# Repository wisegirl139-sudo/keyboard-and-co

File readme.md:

<h2 align="centre">Keyboard & co</h2>
hi,welcome to my little disaterously organised project, now keyboard&co is a modular keyboard made by Oliver and me , now im good at websites and schmatics apparently but pcbs are not my thinggg. 
the modular keyboard uses a esp32 s3 vroom , and pogo pins i think theyre called to connect each part of the keyboard. then it uses the same switches as a hack pad. bom etc is to come soon , journal rn is time lapses but will be fully updated by next ship
<h4>SCH</h4>

okay well that was that , now for my expertise which is web dev , i present to u the most me website i have ever made. it has media pipe for gesture control , yes its gesture controlled yeas u can flip off the laptop , it scrolls the page, maybe give it a thumbs up to select or pinc to zoomin
also featuring my veryyy creapy art lowk
its meant to be a keycap with hena bc happy diwali everyone!!
im not the best artist but atleast i have hope ig
anyways libraries used were ediapipe and three.js for the 3d models made by oliver , u can add and interact with them using ur cursor too!! and download files does spam you but its cool
anyways that all for now, gonna finish journal then yes adios

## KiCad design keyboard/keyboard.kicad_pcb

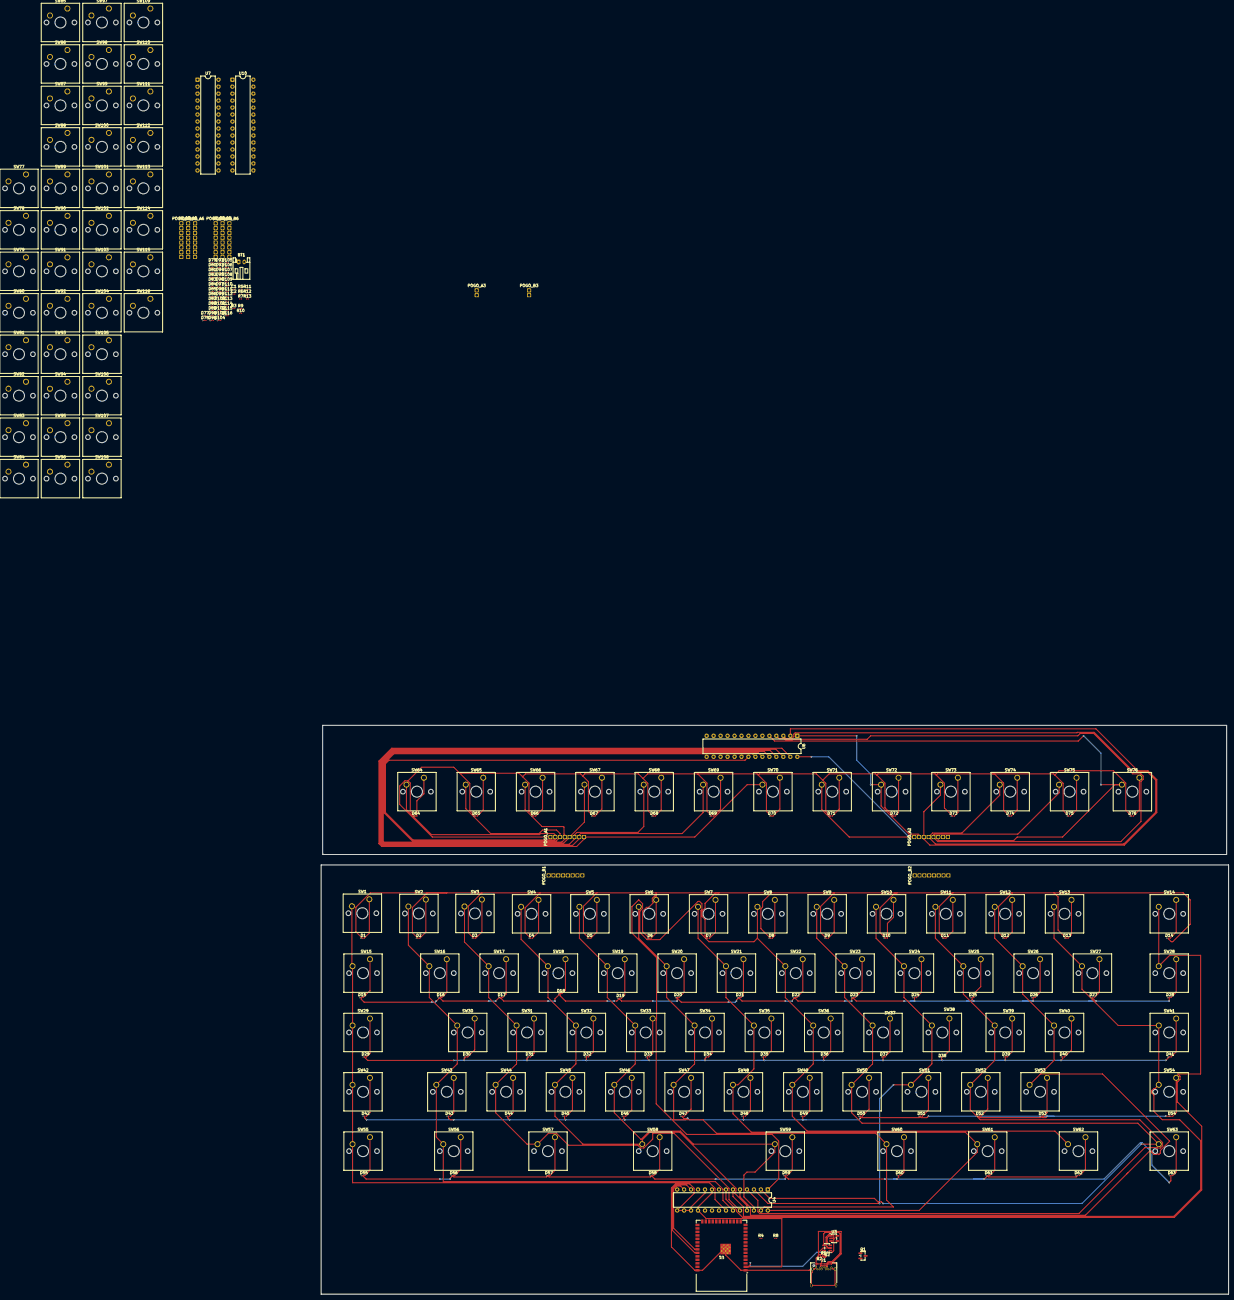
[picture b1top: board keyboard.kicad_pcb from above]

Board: 2 copper layers, 330.2 x 207.0 mm, 269 parts (0 on the bottom side), 189 nets.

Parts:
BT1: Battery_Cell; JST_PH_S2B-PH-K_1x02_P2.00mm_Horizontal
C1: 10uf; C_0201_0603Metric
C2: 100n; C_0201_0603Metric
D1, D2, D3, D4, D5, D6, D7, D8, D9, D10, D11, D12, D13, D14, D15, D16, D17, D18, D19, D20, D21, D22, D23, D24, D25, D26, D27, D28, D29, D30, D31, D32, D33, D34, D35, D36, D37, D38, D39, D40, D41, D42, D43, D44, D45, D46, D47, D48, D49, D50, D51, D52, D53, D54, D55, D56, D57, D58, D59, D60, D61, D62, D63, D64, D65, D66, D67, D68, D69, D70, D71, D72, D73, D74, D75, D76, D77, D78, D79, D80, D81, D82, D83, D84, D85, D86, D87, D88, D89, D90, D91, D92, D93, D94, D95, D96, D97, D98, D99, D100, D101, D102, D103, D104, D105, D106, D107, D108, D109, D110, D111, D112, D113, D114, D115, D116: LED; LED_0201_0603Metric
J1: USB_C_Receptacle; USB_C_Receptacle_Amphenol_12401548E4-2A
POGO_A1, POGO_A2, POGO_A4, POGO_A5, POGO_A6: 8_Pin
POGO_A3: 2_Pin
POGO_B1, POGO_B2, POGO_B4, POGO_B5, POGO_B6: 8_Pin
POGO_B3: 2_Pin
Q1: AO3401A; SOT-23
R1: R; R_0201_0603Metric
R2, R3: 5.1k; R_0201_0603Metric
R4, R5, R8: 100k; R_0201_0603Metric
R6, R7, R10, R11, R12, R13: 4.7k; R_0201_0603Metric
R9: 330; R_0201_0603Metric
SW1, SW2, SW3, SW4, SW5, SW6, SW7, SW8, SW9, SW10, SW11, SW12, SW13, SW14, SW15, SW16, SW17, SW18, SW19, SW20, SW21, SW22, SW23, SW24, SW25, SW26, SW27, SW28, SW29, SW30, SW31, SW32, SW33, SW34, SW35, SW36, SW37, SW38, SW39, SW40, SW41, SW42, SW43, SW44, SW45, SW46, SW47, SW48, SW49, SW50, SW51, SW52, SW53, SW54, SW55, SW56, SW57, SW58, SW59, SW60, SW61, SW62, SW63, SW64, SW65, SW66, SW67, SW68, SW69, SW70, SW71, SW72, SW73, SW74, SW75, SW76, SW77, SW78, SW79, SW80, SW81, SW82, SW83, SW84, SW85, SW86, SW87, SW88, SW89, SW90, SW91, SW92, SW93, SW94, SW95, SW96, SW97, SW98, SW99, SW100, SW101, SW102, SW103, SW104, SW105, SW106, SW107, SW108, SW109, SW110, SW111, SW112, SW113, SW114, SW115, SW116: SW_Push; SW_Cherry_MX_1.00u_PCB
U1: ESP32-S3-WROOM-1
U2: MCP73831-2-OT; SOT-23-5
U3: AP2112K-3.3; SOT-23-5
U4, U6, U7, U10: MCP23017x-x-SP; DIP-28_W7.62mm

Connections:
+3V3: C1.2, C2.1, POGO_A6.1, POGO_B6.1, R6.2, R7.2, R10.2, R11.2, R12.2, R13.2, U1.2 (3V3), U3.5 (VOUT), U4.9 (V_{DD}), U4.18 (~RESET), U6.9 (V_{DD}), U6.18 (~RESET), U7.9 (V_{DD}), U7.18 (~RESET), U10.9 (V_{DD}), U10.15 (A0), U10.18 (~RESET)
+5V: J1.A4 (VBUS), J1.A9 (VBUS), J1.B4 (VBUS), J1.B9 (VBUS), U2.4 (V_{DD})
C0: POGO_A1.2, POGO_B1.2, SW64.2, U6.21 (GPA0)
C1: POGO_A1.3, POGO_B1.3, SW65.2, U6.22 (GPA1)
C2: POGO_A1.4, POGO_B1.4, SW66.2, U6.23 (GPA2)
C3: POGO_A1.5, POGO_B1.5, SW67.2, U6.24 (GPA3)
C4: POGO_A1.6, POGO_B1.6, SW68.2, U6.25 (GPA4)
C5: POGO_A1.7, POGO_B1.7, SW69.2, U6.26 (GPA5)
C6: POGO_A1.8, POGO_B1.8, SW70.2, U6.27 (GPA6)
C7: POGO_A2.1, POGO_B2.1, SW71.2, U6.28 (GPA7)
C8: POGO_A2.2, POGO_B2.2, SW72.2, U6.1 (GPB0)
C9: POGO_A2.3, POGO_B2.3, SW73.2, U6.2 (GPB1)
C10: POGO_A2.4, POGO_B2.4, SW74.2, U6.3 (GPB2)
C11: POGO_A2.5, POGO_B2.5, SW75.2, U6.4 (GPB3)
C12: POGO_A2.6, POGO_B2.6, SW76.2, U6.5 (GPB4)
GND: BT1.1 (+), C1.1, C2.2, J1.A1 (GND), J1.A12 (GND), J1.B1 (GND), J1.B12 (GND), J1.SH (SHIELD), POGO_A2.8, POGO_A3.2, POGO_A4.8, POGO_A6.2, POGO_A6.8, POGO_B2.8, POGO_B3.2, POGO_B4.8, POGO_B6.2, POGO_B6.8, R1.2, R2.2, R3.2, R5.1, U1.1 (GND), U1.40 (GND), U1.41 (GND), U2.2 (V_{SS}), U3.2 (GND), U4.10 (V_{SS}), U4.15 (A0), U4.16 (A1), U4.17 (A2), U6.10 (V_{SS}), U6.15 (A0), U6.16 (A1), U6.17 (A2), U7.10 (V_{SS}), U7.15 (A0), U7.16 (A1), U7.17 (A2), U10.10 (V_{SS}), U10.16 (A1), U10.17 (A2)
unnamed: D1.2 (A), SW1.1
unnamed: D2.2 (A), SW2.1
unnamed: D3.2 (A), SW3.1
unnamed: D4.2 (A), SW4.1
unnamed: D5.2 (A), SW5.1
unnamed: D6.2 (A), SW6.1
unnamed: D7.2 (A), SW7.1
unnamed: D8.2 (A), SW8.1
unnamed: D9.2 (A), SW9.1
unnamed: D10.2 (A), SW10.1
unnamed: D11.2 (A), SW11.1
unnamed: D12.2 (A), SW12.1
unnamed: D13.2 (A), SW13.1
unnamed: D14.2 (A), SW14.1
unnamed: D15.2 (A), SW15.1
unnamed: D16.2 (A), SW16.1
unnamed: D17.2 (A), SW17.1
unnamed: D18.2 (A), SW18.1
unnamed: D19.2 (A), SW19.1
unnamed: D20.2 (A), SW20.1
unnamed: D21.2 (A), SW21.1
unnamed: D22.2 (A), SW22.1
unnamed: D23.2 (A), SW23.1
unnamed: D24.2 (A), SW24.1
unnamed: D25.2 (A), SW25.1
unnamed: D26.2 (A), SW26.1
unnamed: D27.2 (A), SW27.1
unnamed: D28.2 (A), SW28.1
unnamed: D29.2 (A), SW29.1
unnamed: D30.2 (A), SW30.1
unnamed: D31.2 (A), SW31.1
unnamed: D32.2 (A), SW32.1
unnamed: D33.2 (A), SW33.1
unnamed: D34.2 (A), SW34.1
unnamed: D35.2 (A), SW35.1
unnamed: D36.2 (A), SW36.1
unnamed: D37.2 (A), SW37.1
unnamed: D38.2 (A), SW38.1
unnamed: D39.2 (A), SW39.1
unnamed: D40.2 (A), SW40.1
unnamed: D41.2 (A), SW41.1
unnamed: D42.2 (A), SW42.1
unnamed: D43.2 (A), SW43.1
unnamed: D44.2 (A), SW44.1
unnamed: D45.2 (A), SW45.1
unnamed: D46.2 (A), SW46.1
unnamed: D47.2 (A), SW47.1
unnamed: D48.2 (A), SW48.1
unnamed: D49.2 (A), SW49.1
unnamed: D50.2 (A), SW50.1
unnamed: D51.2 (A), SW51.1
unnamed: D52.2 (A), SW52.1
unnamed: D53.2 (A), SW53.1
unnamed: D54.2 (A), SW54.1
unnamed: D55.2 (A), SW55.1
unnamed: D56.2 (A), SW56.1
unnamed: D57.2 (A), SW57.1
unnamed: D58.2 (A), SW58.1
unnamed: D59.2 (A), SW59.1
unnamed: D60.2 (A), SW60.1
unnamed: D61.2 (A), SW61.1
unnamed: D62.2 (A), SW62.1
unnamed: D63.2 (A), SW63.1
unnamed: D64.2 (A), SW64.1
unnamed: D65.2 (A), SW65.1
unnamed: D66.2 (A), SW66.1
unnamed: D67.2 (A), SW67.1
unnamed: D68.2 (A), SW68.1
unnamed: D69.2 (A), SW69.1
unnamed: D70.2 (A), SW70.1
unnamed: D71.2 (A), SW71.1
unnamed: D72.2 (A), SW72.1
unnamed: D73.2 (A), SW73.1
unnamed: D74.2 (A), SW74.1
unnamed: D75.2 (A), SW75.1
unnamed: D76.2 (A), SW76.1
unnamed: D77.2 (A), SW77.1
unnamed: D78.2 (A), SW78.1
unnamed: D79.2 (A), SW79.1
unnamed: D80.2 (A), SW80.1
unnamed: D81.2 (A), SW81.1
unnamed: D82.2 (A), SW82.1
unnamed: D83.2 (A), SW83.1
unnamed: D84.2 (A), SW86.1
unnamed: D85.2 (A), SW89.1
unnamed: D86.2 (A), SW93.1
unnamed: D87.2 (A), SW94.1
unnamed: D88.2 (A), SW95.1
unnamed: D89.2 (A), SW92.1
unnamed: D90.2 (A), SW90.1
unnamed: D91.2 (A), SW87.1
unnamed: D92.2 (A), SW84.1
unnamed: D93.2 (A), SW85.1
unnamed: D94.2 (A), SW88.1
unnamed: D95.2 (A), SW91.1
unnamed: D96.2 (A), SW96.1
unnamed: D97.2 (A), SW97.1
unnamed: D98.2 (A), SW98.1
unnamed: D99.2 (A), SW99.1
unnamed: D100.2 (A), SW100.1
unnamed: D101.2 (A), SW101.1
unnamed: D102.2 (A), SW102.1
unnamed: D103.2 (A), SW103.1
unnamed: D104.2 (A), SW104.1
unnamed: D105.2 (A), SW105.1
unnamed: D106.2 (A), SW106.1
unnamed: D107.2 (A), SW107.1
unnamed: D108.2 (A), SW108.1
unnamed: D109.2 (A), SW109.1
unnamed: D110.2 (A), SW110.1
unnamed: D111.2 (A), SW111.1
unnamed: D112.2 (A), SW112.1
unnamed: D113.2 (A), SW113.1
unnamed: D114.2 (A), SW114.1
unnamed: D115.2 (A), SW115.1
unnamed: D116.2 (A), SW116.1
unnamed: J1.A5 (CC1), R2.1
unnamed: J1.B5 (CC2), R3.1
unnamed: R9.2, U1.38 (IO2)
unnamed: R1.1, U2.5 (PROG)
R0: D64.1 (K), D65.1 (K), D66.1 (K), D67.1 (K), D68.1 (K), D69.1 (K), D70.1 (K), D71.1 (K), D72.1 (K), D73.1 (K), D74.1 (K), D75.1 (K), D76.1 (K), POGO_A1.1, POGO_B1.1
adc: R4.1, R5.2, U1.39 (IO1)
bat: BT1.2 (-), Q1.2 (S), R4.2, R8.1, U2.3 (V_{BAT}), U3.1 (VIN)
c0: SW1.2, SW15.2, SW29.2, SW42.2, SW55.2, U4.22 (GPA1)
c1: SW2.2, SW16.2, SW30.2, SW43.2, SW56.2, U4.23 (GPA2)
c2: SW3.2, SW17.2, SW31.2, SW44.2, SW57.2, U4.24 (GPA3)
c3: SW4.2, SW18.2, SW32.2, SW45.2, SW58.2, U4.25 (GPA4)
c4: SW5.2, SW19.2, SW33.2, SW46.2, SW59.2, U4.26 (GPA5)
c5: SW6.2, SW20.2, SW34.2, SW47.2, SW60.2, U4.27 (GPA6)
c6: SW7.2, SW21.2, SW35.2, SW48.2, SW61.2, U4.28 (GPA7)
c7: SW8.2, SW22.2, SW36.2, SW49.2, SW62.2, U4.1 (GPB0)
c8: SW9.2, SW23.2, SW37.2, SW50.2, SW63.2, U4.2 (GPB1)
c9: SW10.2, SW24.2, SW38.2, SW51.2, U4.3 (GPB2)
c10: SW11.2, SW25.2, SW39.2, SW52.2, U4.4 (GPB3)
c11: SW12.2, SW26.2, SW40.2, SW53.2, U4.5 (GPB4)
c12: SW13.2, SW27.2, SW41.2, SW54.2, U4.6 (GPB5)
c13: SW14.2, SW28.2, U4.7 (GPB6)
c*0: POGO_A5.5, POGO_B5.4, SW83.2, SW84.2, SW85.2, U7.21 (GPA0)
c*1: POGO_A5.4, POGO_B5.5, SW86.2, SW87.2, SW88.2, U7.22 (GPA1)
c*2: POGO_A5.3, POGO_B5.6, SW89.2, SW90.2, SW91.2, U7.23 (GPA2)
c*3: POGO_A5.2, POGO_B5.7, SW92.2, U7.24 (GPA3)
c*4: POGO_A5.1, POGO_B5.8, SW93.2, SW94.2, SW95.2, U7.25 (GPA4)
c-0: SW96.2, SW102.2, SW108.2, SW113.2, U10.25 (GPA4)
c-1: SW97.2, SW103.2, SW109.2, SW114.2, U10.26 (GPA5)
c-2: SW98.2, SW104.2, SW110.2, SW115.2, U10.27 (GPA6)
c-3: SW99.2, SW105.2, SW111.2, U10.28 (GPA7)
c-4: SW100.2, SW106.2, SW112.2, SW116.2, U10.1 (GPB0)
c-5: SW101.2, SW107.2, U10.2 (GPB1)
c_0: POGO_A4.7, POGO_B4.7, SW77.2, SW78.2, SW79.2, SW80.2, SW81.2, SW82.2, U4.21 (GPA0)
int: POGO_A6.5, POGO_B6.5, U10.20 (INTA)
leden: Q1.1 (G), R8.2, U1.33 (IO40)
ledin: POGO_A2.7, POGO_A6.6, POGO_B2.7, POGO_B6.6, R9.1
r0: D1.1 (K), D2.1 (K), D3.1 (K), D4.1 (K), D5.1 (K), D6.1 (K), D7.1 (K), D8.1 (K), D9.1 (K), D10.1 (K), D11.1 (K), D12.1 (K), D13.1 (K), D14.1 (K), U1.4 (IO4)
r1: D15.1 (K), D16.1 (K), D17.1 (K), D18.1 (K), D19.1 (K), D20.1 (K), D21.1 (K), D22.1 (K), D23.1 (K), D24.1 (K), D25.1 (K), D26.1 (K), D27.1 (K), D28.1 (K), U1.5 (IO5)
r2: D29.1 (K), D30.1 (K), D31.1 (K), D32.1 (K), D33.1 (K), D34.1 (K), D35.1 (K), D36.1 (K), D37.1 (K), D38.1 (K), D39.1 (K), D40.1 (K), D41.1 (K), U1.6 (IO6)
r3: D42.1 (K), D43.1 (K), D44.1 (K), D45.1 (K), D46.1 (K), D47.1 (K), D48.1 (K), D49.1 (K), D50.1 (K), D51.1 (K), D52.1 (K), D53.1 (K), D54.1 (K), U1.7 (IO7)
r4: D55.1 (K), D56.1 (K), D57.1 (K), D58.1 (K), D59.1 (K), D60.1 (K), D61.1 (K), D62.1 (K), D63.1 (K), U1.12 (IO8)
r*0: D83.1 (K), D84.1 (K), D85.1 (K), D86.1 (K), POGO_A5.8, POGO_B5.1, U1.10 (IO17)
r*1: D87.1 (K), D89.1 (K), D90.1 (K), D91.1 (K), D92.1 (K), POGO_A5.7, POGO_B5.2, U1.11 (IO18)
r*2: D88.1 (K), D93.1 (K), D94.1 (K), D95.1 (K), POGO_A5.6, POGO_B5.3, U1.23 (IO21)
r-0: D96.1 (K), D97.1 (K), D98.1 (K), D99.1 (K), D100.1 (K), D101.1 (K), U10.21 (GPA0)
r-1: D102.1 (K), D103.1 (K), D104.1 (K), D105.1 (K), D106.1 (K), D107.1 (K), U10.22 (GPA1)
r-2: D108.1 (K), D109.1 (K), D110.1 (K), D111.1 (K), D112.1 (K), U10.23 (GPA2)
r-3: D113.1 (K), D114.1 (K), D115.1 (K), D116.1 (K), U10.24 (GPA3)
r_0: D77.1 (K), POGO_A4.1, POGO_B4.1, U1.17 (IO9)
r_1: D78.1 (K), POGO_A4.2, POGO_B4.2, U1.18 (IO10)
r_2: D79.1 (K), POGO_A4.3, POGO_B4.3, U1.19 (IO11)
r_3: D80.1 (K), POGO_A4.4, POGO_B4.4
r_4: D81.1 (K), POGO_A4.5, POGO_B4.5, U1.21 (IO13)
r_5: D82.1 (K), POGO_A4.6, POGO_B4.6, U1.22 (IO14)
scl: POGO_A6.4, POGO_B6.4, R7.1, R10.1, R12.1, U1.35 (IO42), U4.12 (SCK), U6.12 (SCK), U7.12 (SCK), U10.12 (SCK)
sda: POGO_A6.3, POGO_B6.3, R6.1, R11.1, R13.1, U1.34 (IO41), U4.13 (SDA), U6.13 (SDA), U7.13 (SDA), U10.13 (SDA)
vled: POGO_A3.1, POGO_A6.7, POGO_B3.1, POGO_B6.7, Q1.3 (D)
